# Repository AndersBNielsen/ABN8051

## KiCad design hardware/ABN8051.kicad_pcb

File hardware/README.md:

# ABN8051 hardware (rev 0.2, unrouted)

KiCad 10 project for the DOS/51 board described in [`../emulator/docs/HARDWARE.md`](../emulator/docs/HARDWARE.md): schematic, 100 × 89 mm floor plan and silkscreen. **No tracks are routed** and nothing here has been built or bench-tested.

## What is on the board

| Block | Parts | Notes |
| --- | --- | --- |
| CPU | U1 P80C31SFPN, Y1 11.0592 MHz, RC reset + button | EA tied low |
| Address latch | U2 SN74ALS873BNT (DIP-24) | as in the iMania breadboard guide |
| ROM | U3 W27C512 or 27C256 | CODE 0000–7FFF. JP1 sets pin 1: LO/HI half of a W27C512, HI for 27C256 (Vpp = 5 V) |
| RAM0 | U4 62256 (or 6264) | XDATA 0000–7FFF. Footprint takes a 600 mil or a 300 mil (skinny) DIP-28 |
| RAM1 | U5 62256 (or 6264) | CODE + XDATA 8000–FFFF. 600 or 300 mil, like U4 |
| Glue | U6 74LS00/74HCT00 | ~A15, RAM1 ~OE = ~RD AND ~PSEN, spare gate gives ~RST |
| USB | J1 USB-C (5k1 on CC1/CC2), F1 polyfuse, SW1, U8 CH340G, Y2 12 MHz MA-406 | 57600 8N1 console. R9 (1k) lets an adapter on J4 override the CH340 |
| microSD | J6 Hirose DM3CS-SF, U9 KF33 **or** U11 MIC5504-3.3 (3.3 V), U10 74LVC08 as 5 V → 3.3 V shifter | P1.4 CS, P1.5 SCK, P1.6 MOSI, P1.7 MISO, same as the emulator |
| I/O | J2 2×20 bus, J3 2×6 port 1, J4 UART, J5 I/O selects, J7 5 V | 2.54 mm headers |
| Optional | U7 74HC138 | ~IOn is low in 8 K block n (n × 2000h). Not qualified by a strobe |
| User | D1–D4 on P1.0–P1.3 (active low, JP5 disables), INT0/INT1 buttons, power LED | matches the DOS/51 examples. SW2–SW4 take a TL3342 or a 3×6 mm 2-pin SMD tact switch (iMania FC-003D-5.0) fitted 90° on the same centre |

Solder jumpers JP2–JP6 are on the **bottom**, each labelled next to its pads. JP2/JP3 select 62256 (pin 26 = A13, default) or 6264 (pin 26 = CS2 high; the 8 K then repeats through the 32 K block). JP4 moves RAM1's chip select from ~A15 to ~IO4 (8000–9FFF) so A000–FFFF is free for add-ons; this needs U7. JP6 connects the card-detect switch to T0.

## Things to check before ordering

- **FC-003D-5.0 land pattern** is borrowed from the XKB TS-1101 3×6 mm drawing (pad centres 7.5 mm); the FC-003D has no datasheet. Check the lead span of a real part against the 1:1 print.
- **U9 or U11, never both.** With the KF33 (U9) C18 must be the tantalum (KF33 needs output ESR 0.1–10 Ω); with the MIC5504 (U11, MLCC-stable) fit a 10 µF 1206 MLCC in C18's pads. C20 is 1 µF for both.

- **DM3CS-SF footprint** (`ABN8051.pretty`) was drawn from Hirose drawing EDC3-327223-03. Pin order and the detect/shell pad assignment were read from that drawing; print 1:1 and check against a real holder.
- **KF33 inhibit** (pin 5) is tied to GND on the assumption that low = on. ST's datasheet text does not state the polarity outright.
- **SW1** uses a generic 2.54 mm-pitch slide switch footprint (centre pin common). Fit any ≥ 300 mA part, or a wire link between pins 1 and 2.
- **P1.4–P1.7 are driven/loaded by the SD interface** (U10 drives P1.7 through 330 Ω), so on J3 they are monitor points rather than free GPIO.
- 22 pF is used on both crystals to keep one BOM line; the MA-406 is specified for 10 pF load, so 12–15 pF would be closer.
- U6 is listed as 74LS00 because that is what iMania stocks; 74HCT00 also works.
- LCSC numbers are in the `LCSC` field, iMania product ids in the `iMania` field (`ABN8051-BOM.csv`). On the DIP parts the LCSC number is the **socket** (as in the 65uino project), since the chips come from iMania stock.

## Regenerating

`tools/design.py` generated the schematic and `tools/pcbgen.py` the board. **Running `pcbgen.py` overwrites `ABN8051.kicad_pcb`, including any routing.** After the first manual edit, treat the KiCad files as the source and use Update PCB from Schematic instead.

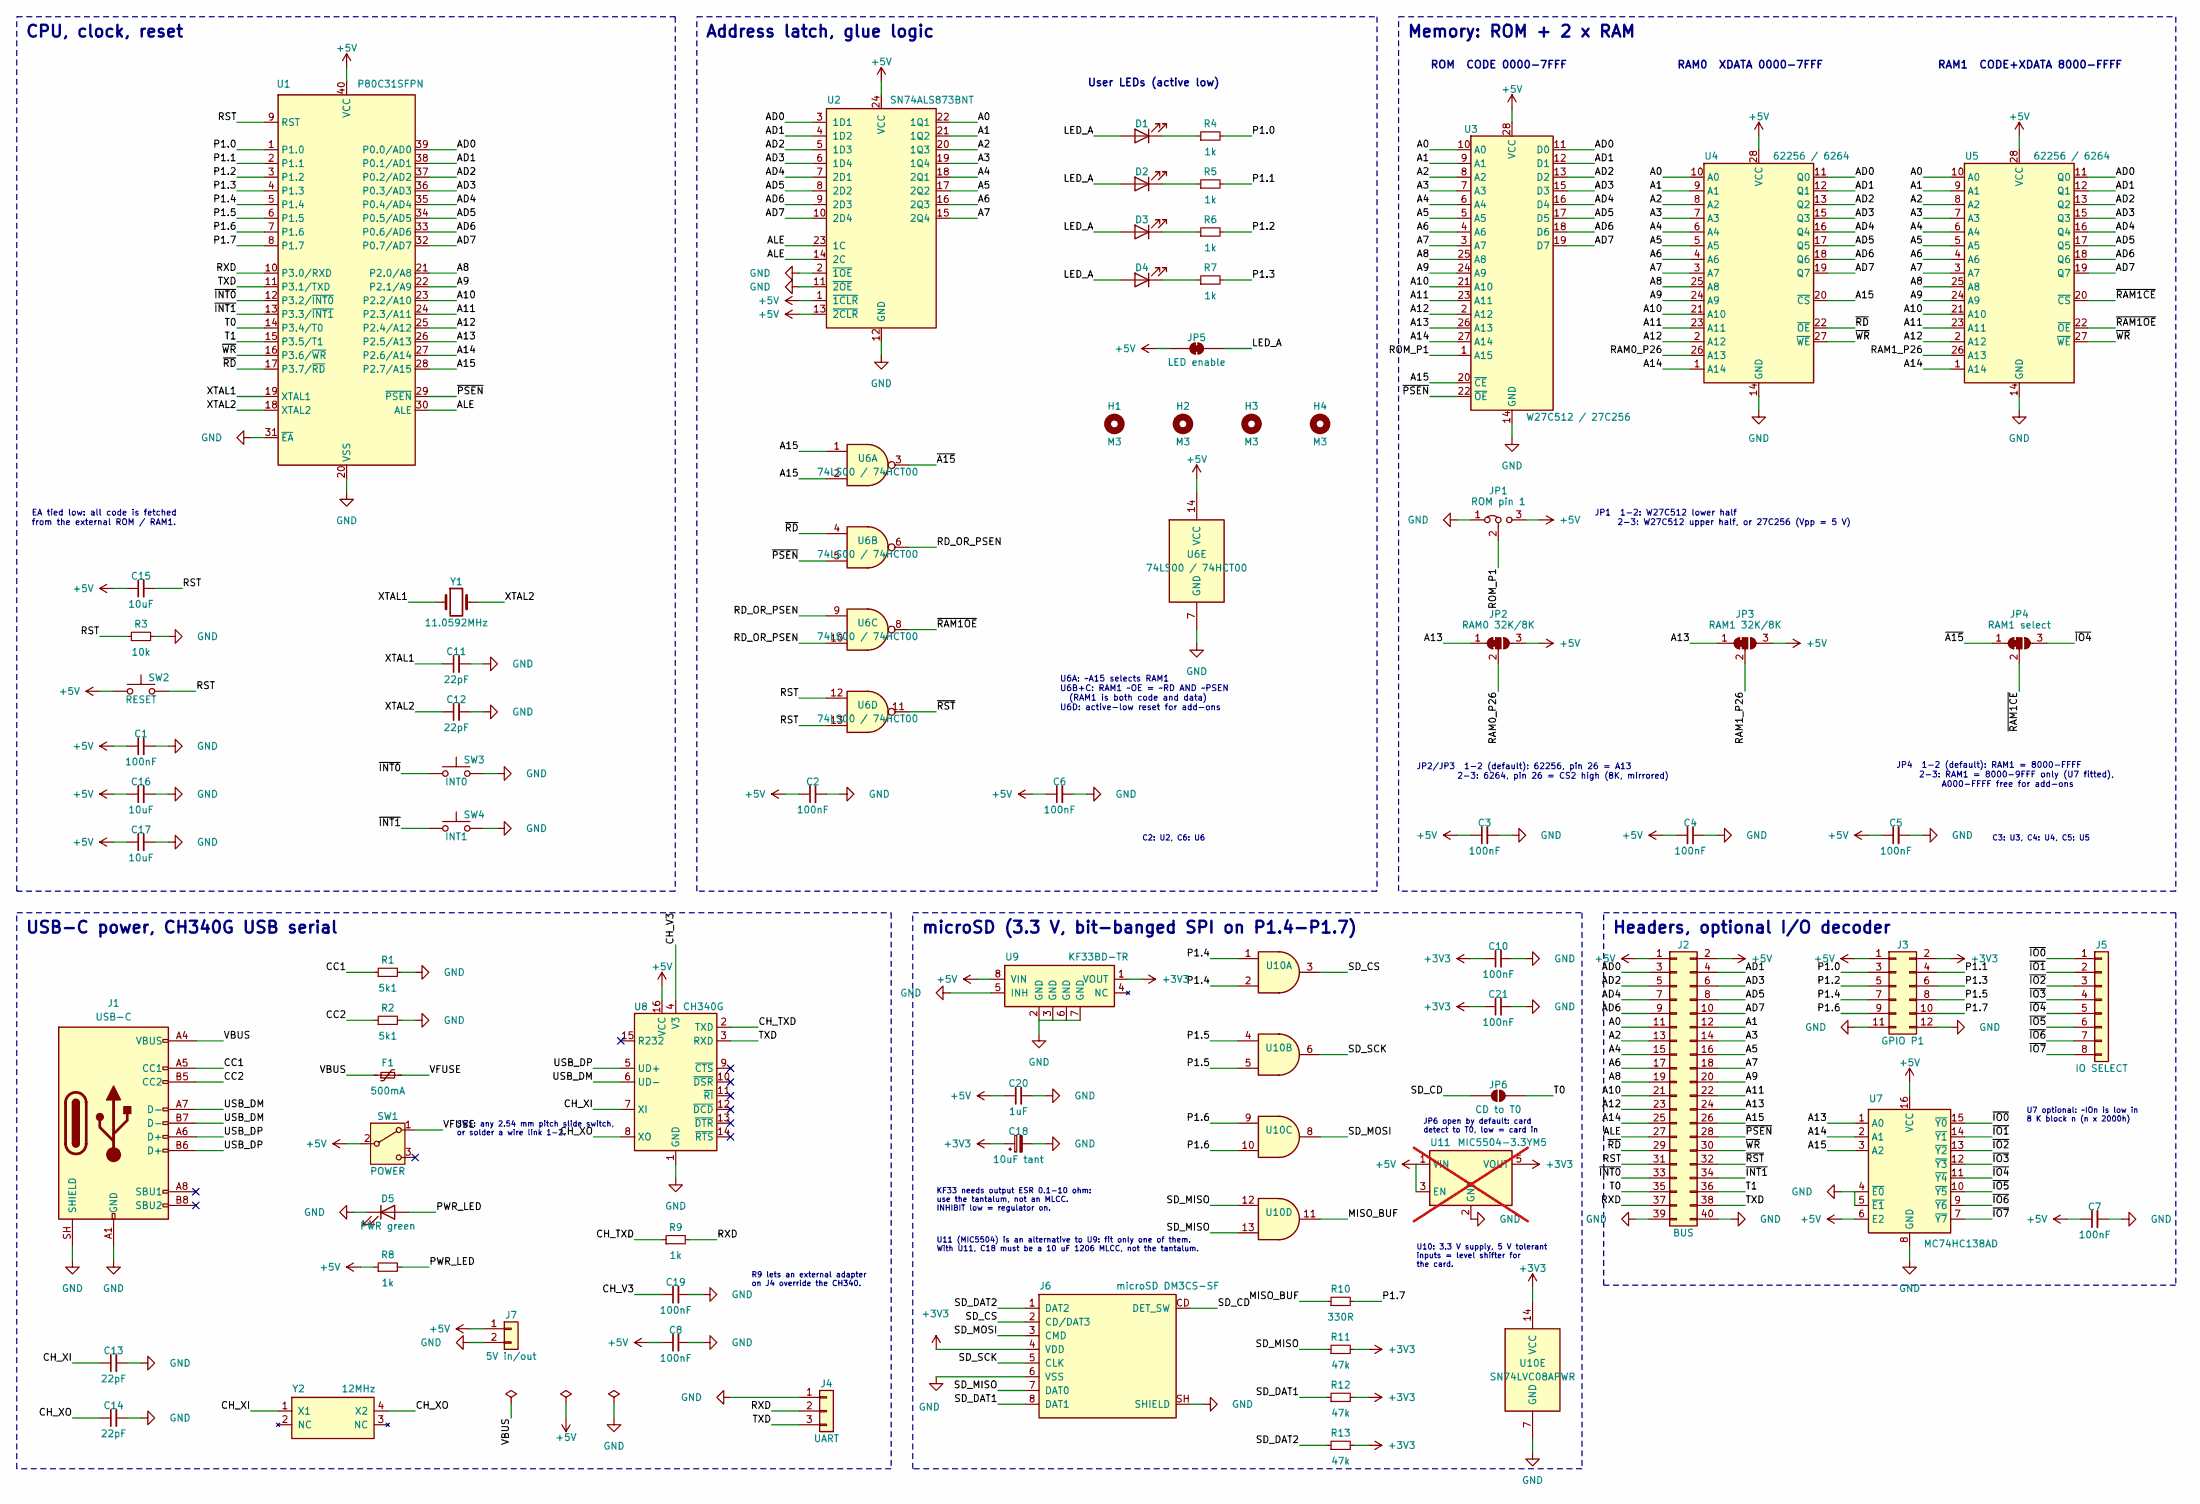
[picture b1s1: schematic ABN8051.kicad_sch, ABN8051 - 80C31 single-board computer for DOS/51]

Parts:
C1, C2, C3, C4, C5, C6, C7, C8, C10, C19, C21: 100nF; C_0805_2012Metric; LCSC C49678
C11, C12, C13, C14: 22pF; C_0805_2012Metric; LCSC C1804
C15, C16, C17: 10uF; C_1206_3216Metric; LCSC C13585
C18: 10uF tant; CP_EIA-3216-18_Kemet-A; LCSC C7171
C20: 1uF; C_0805_2012Metric; LCSC C28323
D1, D2, D3, D4: red; LED_0805_2012Metric; LCSC C84256
D5: PWR green; LED_0805_2012Metric; LCSC C2297
F1: 500mA; Fuse_1206_3216Metric; LCSC C20799
H1, H2, H3, H4: M3; MountingHole_3.2mm_M3
J1: USB-C; USB_C_Receptacle_HCTL_HC-TYPE-C-16P-01A; LCSC C2894897
J2: BUS; PinHeader_2x20_P2.54mm_Vertical
J3: GPIO P1; PinHeader_2x06_P2.54mm_Vertical
J4: UART; PinHeader_1x03_P2.54mm_Vertical
J5: IO SELECT; PinHeader_1x08_P2.54mm_Vertical
J6: microSD DM3CS-SF; microSD_Hirose_DM3CS-SF
J7: 5V in/out; PinHeader_1x02_P2.54mm_Vertical
JP1: ROM pin 1; PinHeader_1x03_P2.54mm_Vertical
JP2: RAM0 32K/8K; SolderJumper-3_P1.3mm_Bridged12_RoundedPad1.0x1.5mm
JP3: RAM1 32K/8K; SolderJumper-3_P1.3mm_Bridged12_RoundedPad1.0x1.5mm
JP4: RAM1 select; SolderJumper-3_P1.3mm_Bridged12_RoundedPad1.0x1.5mm
JP5: LED enable; SolderJumper-2_P1.3mm_Bridged_RoundedPad1.0x1.5mm
JP6: CD to T0; SolderJumper-2_P1.3mm_Open_RoundedPad1.0x1.5mm
R1, R2: 5k1; R_0805_2012Metric; LCSC C27834
R3: 10k; R_0805_2012Metric; LCSC C17414
R4, R5, R6, R7, R8, R9: 1k; R_0805_2012Metric; LCSC C17513
R10: 330R; R_0805_2012Metric; LCSC C17630
R11, R12, R13: 47k; R_0805_2012Metric; LCSC C17713
SW1: POWER; SW_Slide-03_Wuerth-WS-SLTV_10x2.5x6.4_P2.54mm
SW2: RESET; SW_SPST_TL3342_or_3x6mm; LCSC C318884
SW3: INT0; SW_SPST_TL3342_or_3x6mm; LCSC C318884
SW4: INT1; SW_SPST_TL3342_or_3x6mm; LCSC C318884
U1: P80C31SFPN; DIP-40_W15.24mm; LCSC C72123
U2: SN74ALS873BNT; DIP-24_W7.62mm
U3: W27C512 / 27C256; DIP-28_W15.24mm; LCSC C72121
U4, U5: 62256 / 6264; DIP-28_W7.62mm_W15.24mm; LCSC C72121
U6: 74LS00 / 74HCT00; DIP-14_W7.62mm; LCSC C2325
U7: MC74HC138AD; SOIC-16_3.9x9.9mm_P1.27mm
U8: CH340G; SOIC-16_3.9x9.9mm_P1.27mm; LCSC C14267
U9: KF33BD-TR; SOIC-8_3.9x4.9mm_P1.27mm
U10: SN74LVC08APWR; TSSOP-14_4.4x5mm_P0.65mm
U11: MIC5504-3.3YM5; SOT-23-5; LCSC C3021093; not fitted
Y1: 11.0592MHz; Crystal_SMD_HC49-SD
Y2: 12MHz; Crystal_SMD_SeikoEpson_MA406-4Pin_11.7x4.0mm

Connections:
+3V3: C10.1, C18.1, C21.1, J3.2, J6.4 (VDD), R11.2, R12.2, R13.2, U9.1 (VOUT), U10.14 (VCC), U11.5 (VOUT)
+5V: C1.1, C2.1, C3.1, C4.1, C5.1, C6.1, C7.1, C8.1, C15.1, C16.1, C17.1, C20.1, J2.1, J2.2, J3.1, J7.1, JP1.3 (B), JP2.3 (B), JP3.3 (B), JP5.1 (A), R8.1, SW1.2 (B), SW2.1, U1.40 (VCC), U2.1 (~1CLR), U2.13 (~2CLR), U2.24 (VCC), U3.28 (VCC), U4.28 (VCC), U5.28 (VCC), U6.14 (VCC), U7.6 (E2), U7.16 (VCC), U8.16 (VCC), U9.8 (VIN), U11.1 (VIN), U11.3 (EN)
/A0: J2.11, U2.22 (1Q1), U3.10 (A0), U4.10 (A0), U5.10 (A0)
/A1: J2.12, U2.21 (1Q2), U3.9 (A1), U4.9 (A1), U5.9 (A1)
/A2: J2.13, U2.20 (1Q3), U3.8 (A2), U4.8 (A2), U5.8 (A2)
/A3: J2.14, U2.19 (1Q4), U3.7 (A3), U4.7 (A3), U5.7 (A3)
/A4: J2.15, U2.18 (2Q1), U3.6 (A4), U4.6 (A4), U5.6 (A4)
/A5: J2.16, U2.17 (2Q2), U3.5 (A5), U4.5 (A5), U5.5 (A5)
/A6: J2.17, U2.16 (2Q3), U3.4 (A6), U4.4 (A6), U5.4 (A6)
/A7: J2.18, U2.15 (2Q4), U3.3 (A7), U4.3 (A7), U5.3 (A7)
/A8: J2.19, U1.21 (P2.0/A8), U3.25 (A8), U4.25 (A8), U5.25 (A8)
/A9: J2.20, U1.22 (P2.1/A9), U3.24 (A9), U4.24 (A9), U5.24 (A9)
/A10: J2.21, U1.23 (P2.2/A10), U3.21 (A10), U4.21 (A10), U5.21 (A10)
/A11: J2.22, U1.24 (P2.3/A11), U3.23 (A11), U4.23 (A11), U5.23 (A11)
/A12: J2.23, U1.25 (P2.4/A12), U3.2 (A12), U4.2 (A12), U5.2 (A12)
/A13: J2.24, JP2.1 (A), JP3.1 (A), U1.26 (P2.5/A13), U3.26 (A13), U7.1 (A0)
/A14: J2.25, U1.27 (P2.6/A14), U3.27 (A14), U4.1 (A14), U5.1 (A14), U7.2 (A1)
/A15: J2.26, U1.28 (P2.7/A15), U3.20 (~CE), U4.20 (~CS), U6.1, U6.2, U7.3 (A2)
/AD0: J2.3, U1.39 (P0.0/AD0), U2.3 (1D1), U3.11 (D0), U4.11 (Q0), U5.11 (Q0)
/AD1: J2.4, U1.38 (P0.1/AD1), U2.4 (1D2), U3.12 (D1), U4.12 (Q1), U5.12 (Q1)
/AD2: J2.5, U1.37 (P0.2/AD2), U2.5 (1D3), U3.13 (D2), U4.13 (Q2), U5.13 (Q2)
/AD3: J2.6, U1.36 (P0.3/AD3), U2.6 (1D4), U3.15 (D3), U4.15 (Q3), U5.15 (Q3)
/AD4: J2.7, U1.35 (P0.4/AD4), U2.7 (2D1), U3.16 (D4), U4.16 (Q4), U5.16 (Q4)
/AD5: J2.8, U1.34 (P0.5/AD5), U2.8 (2D2), U3.17 (D5), U4.17 (Q5), U5.17 (Q5)
/AD6: J2.9, U1.33 (P0.6/AD6), U2.9 (2D3), U3.18 (D6), U4.18 (Q6), U5.18 (Q6)
/AD7: J2.10, U1.32 (P0.7/AD7), U2.10 (2D4), U3.19 (D7), U4.19 (Q7), U5.19 (Q7)
/ALE: J2.27, U1.30 (ALE), U2.14 (2C), U2.23 (1C)
/CC1: J1.A5 (CC1), R1.1
/CC2: J1.B5 (CC2), R2.1
/CH_TXD: R9.1, U8.2 (TXD)
/CH_V3: C19.1, U8.4 (V3)
/CH_XI: C13.1, U8.7 (XI), Y2.1 (X1)
/CH_XO: C14.1, U8.8 (XO), Y2.4 (X2)
/LED_A: D1.2 (A), D2.2 (A), D3.2 (A), D4.2 (A), JP5.2 (B)
/MISO_BUF: R10.1, U10.11
/P1.0: J3.3, R4.2, U1.1 (P1.0)
/P1.1: J3.4, R5.2, U1.2 (P1.1)
/P1.2: J3.5, R6.2, U1.3 (P1.2)
/P1.3: J3.6, R7.2, U1.4 (P1.3)
/P1.4: J3.7, U1.5 (P1.4), U10.1, U10.2
/P1.5: J3.8, U1.6 (P1.5), U10.4, U10.5
/P1.6: J3.9, U1.7 (P1.6), U10.9, U10.10
/P1.7: J3.10, R10.2, U1.8 (P1.7)
/PWR_LED: D5.2 (A), R8.2
/RAM0_P26: JP2.2 (C), U4.26 (A13)
/RAM1_P26: JP3.2 (C), U5.26 (A13)
/RD_OR_PSEN: U6.6, U6.9, U6.10
/ROM_P1: JP1.2 (C), U3.1 (A15)
/RST: C15.2, J2.31, R3.1, SW2.2, U1.9 (RST), U6.12, U6.13
/RXD: J2.37, J4.2, R9.2, U1.10 (P3.0/RXD)
/SD_CD: J6.CD (DET_SW), JP6.1 (A)
/SD_CS: J6.2 (CD/DAT3), U10.3
/SD_DAT1: J6.8 (DAT1), R12.1
/SD_DAT2: J6.1 (DAT2), R13.1
/SD_MISO: J6.7 (DAT0), R11.1, U10.12, U10.13
/SD_MOSI: J6.3 (CMD), U10.8
/SD_SCK: J6.5 (CLK), U10.6
/T0: J2.35, JP6.2 (B), U1.14 (P3.4/T0)
/T1: J2.36, U1.15 (P3.5/T1)
/TXD: J2.38, J4.3, U1.11 (P3.1/TXD), U8.3 (RXD)
/USB_DM: J1.A7 (D-), J1.B7 (D-), U8.6 (UD-)
/USB_DP: J1.A6 (D+), J1.B6 (D+), U8.5 (UD+)
/VBUS: F1.1, J1.A4 (VBUS), J1.A9 (VBUS), J1.B4 (VBUS), J1.B9 (VBUS)
/VFUSE: F1.2, SW1.1 (A)
/XTAL1: C11.1, U1.19 (XTAL1), Y1.1
/XTAL2: C12.1, U1.18 (XTAL2), Y1.2
/~A15: JP4.1 (A), U6.3
/~INT0: J2.33, SW3.1, U1.12 (P3.2/~INT0)
/~INT1: J2.34, SW4.1, U1.13 (P3.3/~INT1)
/~IO0: J5.1, U7.15 (~Y0)
/~IO1: J5.2, U7.14 (~Y1)
/~IO2: J5.3, U7.13 (~Y2)
/~IO3: J5.4, U7.12 (~Y3)
/~IO4: J5.5, JP4.3 (B), U7.11 (~Y4)
/~IO5: J5.6, U7.10 (~Y5)
/~IO6: J5.7, U7.9 (~Y6)
/~IO7: J5.8, U7.7 (~Y7)
/~PSEN: J2.28, U1.29 (~PSEN), U3.22 (~OE), U6.5
/~RAM1CE: JP4.2 (C), U5.20 (~CS)
/~RAM1OE: U5.22 (~OE), U6.8
/~RD: J2.29, U1.17 (P3.7/~RD), U4.22 (~OE), U6.4
/~RST: J2.32, U6.11
/~WR: J2.30, U1.16 (P3.6/~WR), U4.27 (~WE), U5.27 (~WE)
GND: C1.2, C2.2, C3.2, C4.2, C5.2, C6.2, C7.2, C8.2, C10.2, C11.2, C12.2, C13.2, C14.2, C16.2, C17.2, C18.2, C19.2, C20.2, C21.2, D5.1 (K), J1.A1 (GND), J1.A12 (GND), J1.B1 (GND), J1.B12 (GND), J1.SH (SHIELD), J2.39, J2.40, J3.11, J3.12, J4.1, J6.6 (VSS), J6.SH (SHIELD), J7.2, JP1.1 (A), R1.2, R2.2, R3.2, SW3.2, SW4.2, U1.20 (VSS), U1.31 (~EA), U2.2 (~1OE), U2.11 (~2OE), U2.12 (GND), U3.14 (GND), U4.14 (GND), U5.14 (GND), U6.7 (GND), U7.4 (~E0), U7.5 (~E1), U7.8 (GND), U8.1 (GND), U9.2 (GND), U9.3 (GND), U9.5 (INH), U9.6 (GND), U9.7 (GND), U10.7 (GND), U11.2 (GND)
unnamed: D1.1 (K), R4.1
unnamed: D2.1 (K), R5.1
unnamed: D3.1 (K), R6.1
unnamed: D4.1 (K), R7.1

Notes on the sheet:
User LEDs (active low)
microSD (3.3 V, bit-banged SPI on P1.4-P1.7)
U11 (MIC5504) is an alternative to U9: fit only one of them. With U11, C18 must be a 10 uF 1206 MLCC, not the tantalum.
SW1: any 2.54 mm pitch slide switch, or solder a wire link 1-2.
U7 optional: ~IOn is low in 8 K block n (n x 2000h)
ROM CODE 0000-7FFF
JP6 open by default: card detect to T0, low = card in
C2: U2, C6: U6
Headers, optional I/O decoder
Memory: ROM + 2 x RAM
Address latch, glue logic
U10: 3.3 V supply, 5 V tolerant inputs = level shifter for the card.
JP4 1-2 (default): RAM1 = 8000-FFFF 2-3: RAM1 = 8000-9FFF only (U7 fitted), A000-FFFF free for add-ons
RAM0 XDATA 0000-7FFF
C3: U3, C4: U4, C5: U5
EA tied low: all code is fetched from the external ROM / RAM1.
KF33 needs output ESR 0.1-10 ohm: use the tantalum, not an MLCC. INHIBIT low = regulator on.
CPU, clock, reset
RAM1 CODE+XDATA 8000-FFFF
JP1 1-2: W27C512 lower half 2-3: W27C512 upper half, or 27C256 (Vpp = 5 V)
U6A: ~A15 selects RAM1 U6B+C: RAM1 ~OE = ~RD AND ~PSEN (RAM1 is both code and data) U6D: active-low reset for add-ons
R9 lets an external adapter on J4 override the CH340.
USB-C power, CH340G USB serial
JP2/JP3 1-2 (default): 62256, pin 26 = A13 2-3: 6264, pin 26 = CS2 high (8K, mirrored)

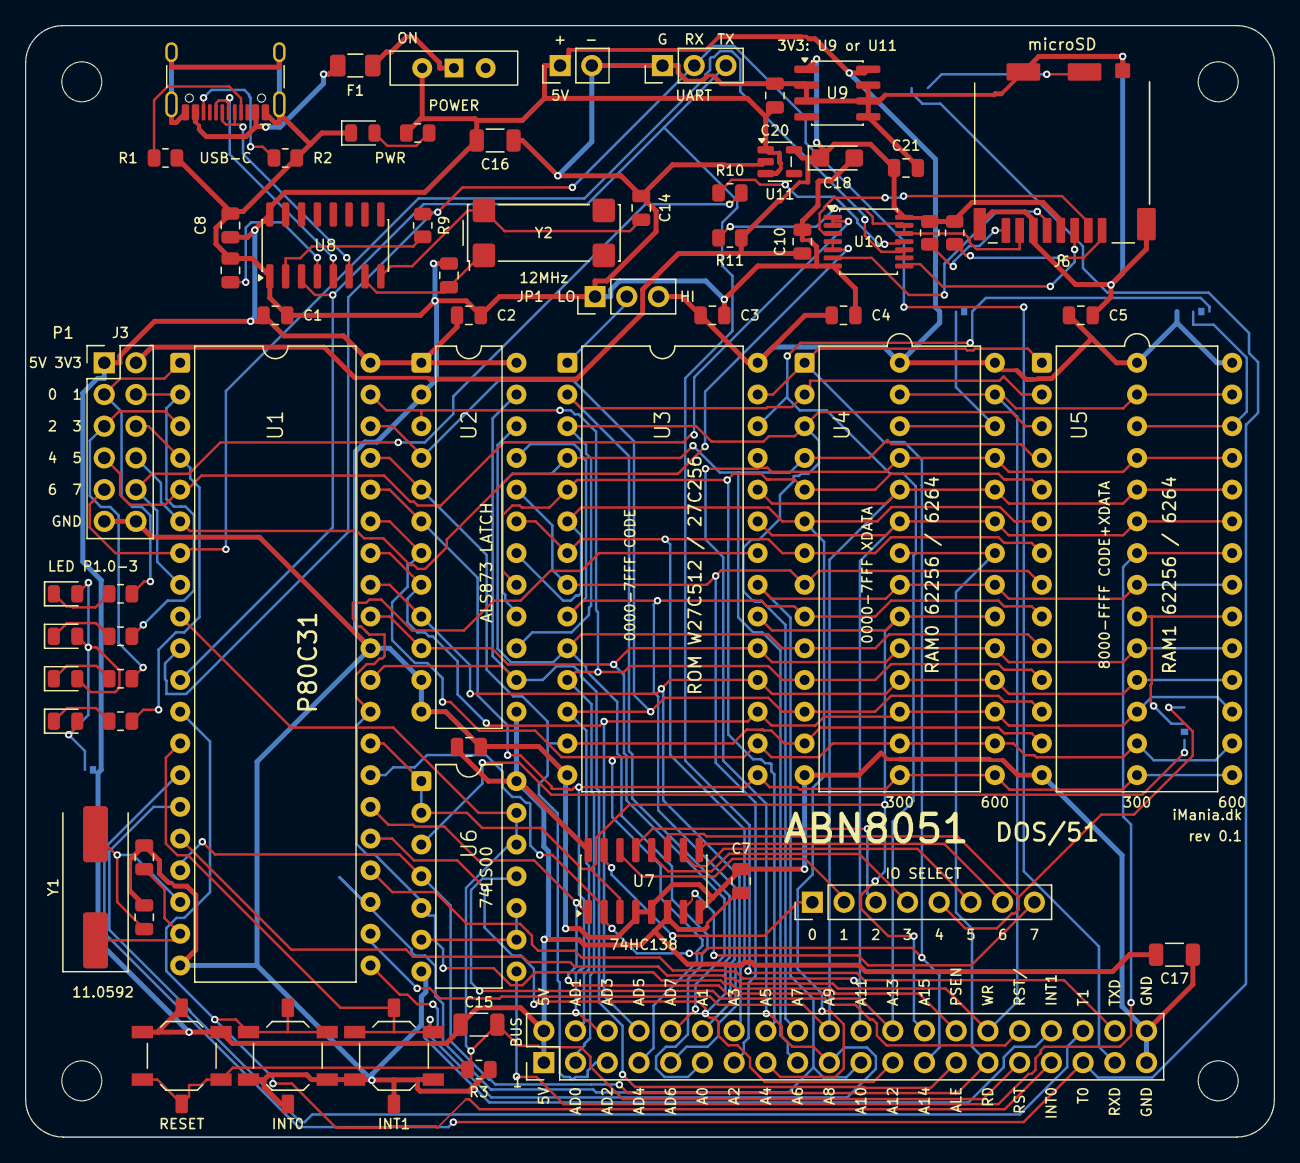
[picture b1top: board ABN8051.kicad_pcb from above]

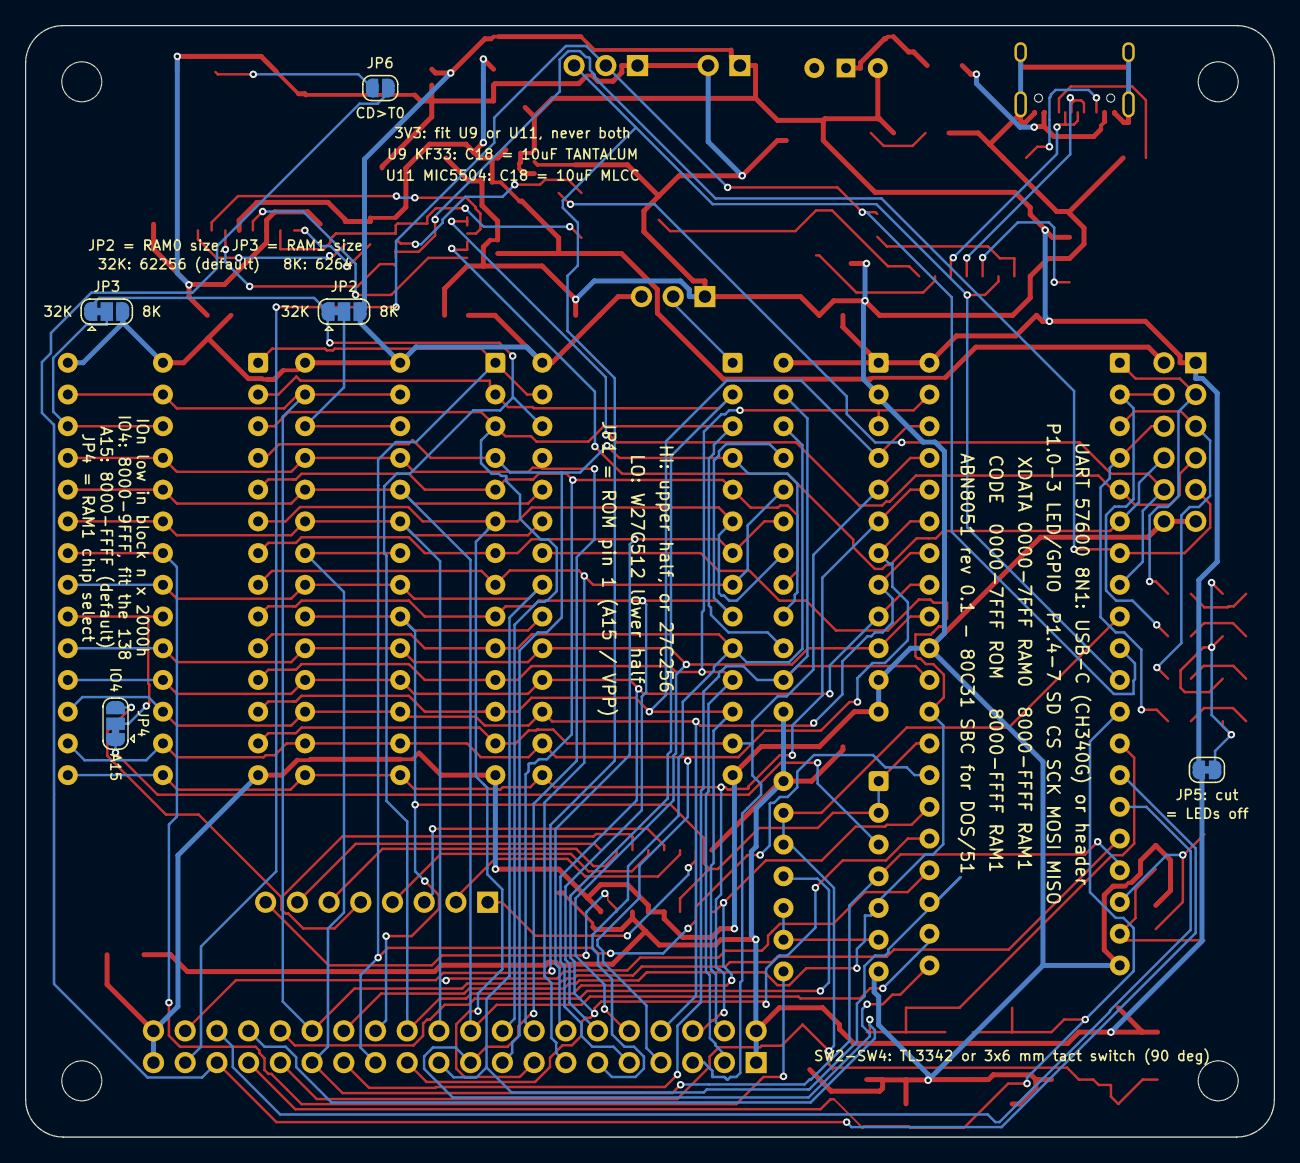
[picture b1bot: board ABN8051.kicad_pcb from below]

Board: 2 copper layers, 100.0 x 89.0 mm, 73 parts (5 on the bottom side), 88 nets.

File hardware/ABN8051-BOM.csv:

"Reference","Value","Footprint","Qty","LCSC","iMania product id","Alternative","Note","DNP"
"C1,C2,C3,C4,C5,C6,C7,C8,C10,C19,C21","100nF","Capacitor_SMD:C_0805_2012Metric","11","C49678","","","",""
"C11,C12,C13,C14","22pF","Capacitor_SMD:C_0805_2012Metric","4","C1804","","","",""
"C15,C16,C17","10uF","Capacitor_SMD:C_1206_3216Metric","3","C13585","","","",""
"C18","10uF tant","Capacitor_Tantalum_SMD:CP_EIA-3216-18_Kemet-A","1","C7171","","With U11: 10uF 1206 MLCC (LCSC C13585)","",""
"C20","1uF","Capacitor_SMD:C_0805_2012Metric","1","C28323","","","",""
"D1,D2,D3,D4","red","LED_SMD:LED_0805_2012Metric","4","C84256","","","",""
"D5","PWR green","LED_SMD:LED_0805_2012Metric","1","C2297","","","",""
"F1","500mA","Fuse:Fuse_1206_3216Metric","1","C20799","","","",""
"H1,H2,H3,H4","M3","MountingHole:MountingHole_3.2mm_M3","4","","","","",""
"J1","USB-C","Connector_USB:USB_C_Receptacle_HCTL_HC-TYPE-C-16P-01A","1","C2894897","","","",""
"J2","BUS","Connector_PinHeader_2.54mm:PinHeader_2x20_P2.54mm_Vertical","1","","","","",""
"J3","GPIO P1","Connector_PinHeader_2.54mm:PinHeader_2x06_P2.54mm_Vertical","1","","","","",""
"J4","UART","Connector_PinHeader_2.54mm:PinHeader_1x03_P2.54mm_Vertical","1","","","","",""
"J5","IO SELECT","Connector_PinHeader_2.54mm:PinHeader_1x08_P2.54mm_Vertical","1","","","","",""
"J6","microSD DM3CS-SF","ABN8051:microSD_Hirose_DM3CS-SF","1","","7589","","",""
"J7","5V in/out","Connector_PinHeader_2.54mm:PinHeader_1x02_P2.54mm_Vertical","1","","","","",""
"JP1","ROM pin 1","Connector_PinHeader_2.54mm:PinHeader_1x03_P2.54mm_Vertical","1","","","","",""
"JP2","RAM0 32K/8K","Jumper:SolderJumper-3_P1.3mm_Bridged12_RoundedPad1.0x1.5mm","1","","","","",""
"JP3","RAM1 32K/8K","Jumper:SolderJumper-3_P1.3mm_Bridged12_RoundedPad1.0x1.5mm","1","","","","",""
"JP4","RAM1 select","Jumper:SolderJumper-3_P1.3mm_Bridged12_RoundedPad1.0x1.5mm","1","","","","",""
"JP5","LED enable","Jumper:SolderJumper-2_P1.3mm_Bridged_RoundedPad1.0x1.5mm","1","","","","",""
"JP6","CD to T0","Jumper:SolderJumper-2_P1.3mm_Open_RoundedPad1.0x1.5mm","1","","","","",""
"R1,R2","5k1","Resistor_SMD:R_0805_2012Metric","2","C27834","","","",""
"R3","10k","Resistor_SMD:R_0805_2012Metric","1","C17414","","","",""
"R4,R5,R6,R7,R8,R9","1k","Resistor_SMD:R_0805_2012Metric","6","C17513","","","",""
"R10","330R","Resistor_SMD:R_0805_2012Metric","1","C17630","","","",""
"R11,R12,R13","47k","Resistor_SMD:R_0805_2012Metric","3","C17713","","","",""
"SW1","POWER","Button_Switch_THT:SW_Slide-03_Wuerth-WS-SLTV_10x2.5x6.4_P2.54mm","1","","","","2.54 mm pitch slide switch >= 300 mA, or wire link 1-2",""
"SW2","RESET","ABN8051:SW_SPST_TL3342_or_3x6mm","1","C318884","","3x6 mm 2-pin SMD tact switch (iMania FC-003D-5.0, 7342)","",""
"SW3","INT0","ABN8051:SW_SPST_TL3342_or_3x6mm","1","C318884","","3x6 mm 2-pin SMD tact switch (iMania FC-003D-5.0, 7342)","",""
"SW4","INT1","ABN8051:SW_SPST_TL3342_or_3x6mm","1","C318884","","3x6 mm 2-pin SMD tact switch (iMania FC-003D-5.0, 7342)","",""
"U1","P80C31SFPN","Package_DIP:DIP-40_W15.24mm","1","C72123","7389","","",""
"U2","SN74ALS873BNT","Package_DIP:DIP-24_W7.62mm","1","","7307","","",""
"U3","W27C512 / 27C256","Package_DIP:DIP-28_W15.24mm","1","C72121","7194","","",""
"U4,U5","62256 / 6264","ABN8051:DIP-28_W7.62mm_W15.24mm","2","C72121","7234","HM6264LP-15 (iMania 7393)","",""
"U6","74LS00 / 74HCT00","Package_DIP:DIP-14_W7.62mm","1","C2325","7450","74HCT00 / 74HC00","",""
"U7","MC74HC138AD","Package_SO:SOIC-16_3.9x9.9mm_P1.27mm","1","","7265","","Optional",""
"U8","CH340G","Package_SO:SOIC-16_3.9x9.9mm_P1.27mm","1","C14267","","","",""
"U9","KF33BD-TR","Package_SO:SOIC-8_3.9x4.9mm_P1.27mm","1","","7345","","",""
"U10","SN74LVC08APWR","Package_SO:TSSOP-14_4.4x5mm_P0.65mm","1","","7520","","",""
"U11","MIC5504-3.3YM5","Package_TO_SOT_SMD:SOT-23-5","1","C3021093","","Alternative to U9: fit U9 or U11, never both","","DNP"
"Y1","11.0592MHz","Crystal:Crystal_SMD_HC49-SD","1","","7354","","",""
"Y2","12MHz","Crystal:Crystal_SMD_SeikoEpson_MA406-4Pin_11.7x4.0mm","1","","7355","","",""
